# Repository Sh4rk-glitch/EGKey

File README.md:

# EGKey (ErgoKey)

A custom ergonomic keyboard PCB design using Choc-style hotswap sockets, a face-down Promicro footprint, and an optional OLED. This repository contains KiCad board sources, generated gerbers, mechanical DXF outlines, and footprint helper scripts driven by a YAML configuration.

---

# Files

## CAD
Inside `EGKey main file` there are many different files below is what is most important and how to get there: 
Starting off with the CAD files, the CAD is under `CAD files`. The main CAD file is `case. step`, if you want the other CAD files then click on `cases` and the rest are in there.
To see the outlines for the CAD go to `config.yaml` and then `output` and then `outlines`.

## PCBs
The PCBs are under `pcbs` then going to `ALL PCBS`. The main PCB file is `EGKeyMasterPCB`, if you wish to see the no routing and my previous attempts at routing then click on `EGKey-noRouting` and `EGKeyPCB-routingV2`.
The gerber file is under `pcbs` then click on the `EGKeyGerb` file, it's a zip file so it'll download as a zip.
Under `config.yaml` the footprint for the mounting hole is there under `footprints` and then its the only file under there.

## Firmware
To get to the firmware file, click on `firmware` which will be under `EGKey main file` and then inside `firmware` will be all the firmware writting for EGKey.

## Bill of Materials
  Part                                 Count                     Cost
- PCB Fab (With Shipping)	               1	                  $30.00 USD
- Arduino Pro Micro	                     1	                  $10.00 USD
- OLED Display	                         1	                   $4.00 USD
- Kailh Choc v2 Switches	               6 (58 Keys Total)	  $30.00 USD
- 1N4148 Diodes (SMD)	                   6 (58 Diodes Total)	 $2.00 USD
- Kailh Choc Hotswap Sockets	           6 (58 Sockets Total)	$10.00 USD
- Reset Switch (SMD, 4 Pin, Flat)	       1	                   $0.50 USD
- Mill Max Sockets & Pins	               1	                   $7.50 USD
- Medium Profile Controller Socket	     1	                   $0.50 USD
- Choc v1 Keycaps	                       1	                  $50-75 USD

Total: $140-160 USD

---
# Pictures:
## PCBs:

## CAD:

All images are located on my journal, at:
[https://blueprint.hackclub.com/projects/5019](url)

If you have any questions, email me at shouryamishra011@gmail.com

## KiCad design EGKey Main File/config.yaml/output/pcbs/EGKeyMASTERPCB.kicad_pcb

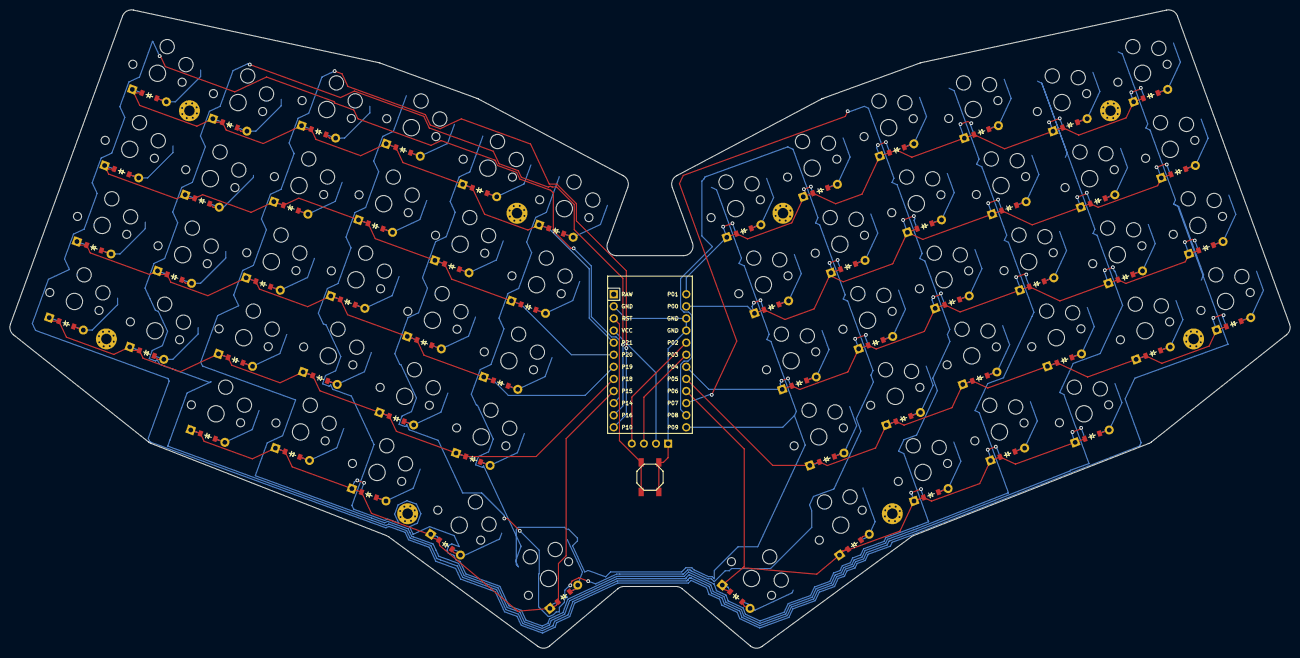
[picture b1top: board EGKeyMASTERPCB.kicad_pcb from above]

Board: 2 copper layers, 268.9 x 134.0 mm, 127 parts (0 on the bottom side), 79 nets.

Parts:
B1: SW_TACT_ALPS_SKQGABE010
D1, D2, D3, D4, D5, D6, D7, D8, D9, D10, D11, D12, D13, D14, D15, D16, D17, D18, D19, D20, D21, D22, D23, D24, D25, D26, D27, D28, D29, D30, D31, D32, D33, D34, D35, D36, D37, D38, D39, D40, D41, D42, D43, D44, D45, D46, D47, D48, D49, D50, D51, D52, D53, D54, D55, D56, D57, D58: ComboDiode
MCU1: ProMicro
OLED1: OLED; OLED_headers
S1, S2, S3, S4, S5, S6, S7, S8, S9, S10, S11, S12, S13, S14, S15, S16, S17, S18, S19, S20, S21, S22, S23, S24, S25, S26, S27, S28, S29, S30, S31, S32, S33, S34, S35, S36, S37, S38, S39, S40, S41, S42, S43, S44, S45, S46, S47, S48, S49, S50, S51, S52, S53, S54, S55, S56, S57, S58: PG1350
_1, _2, _3, _4, _5, _6, _7, _8: MountingHole_2.2mm_M2_Pad_Via

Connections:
GND: B1.1, MCU1.2, MCU1.15, MCU1.16, OLED1.1
P0: D32.1, D36.1, D41.1, D46.1, D51.1, D55.1, MCU1.14
P1: D33.1, D37.1, D42.1, D47.1, D52.1, D56.1, MCU1.13
P2: MCU1.17, OLED1.4
P3: MCU1.18, OLED1.3
P4: D31.1, D35.1, D40.1, D45.1, D50.1, D54.1, MCU1.19
P5: D30.1, D34.1, D39.1, D44.1, D49.1, D53.1, MCU1.20
P6: D38.1, D43.1, D48.1, D57.1, D58.1, MCU1.21
P7: MCU1.22, S15.1, S16.1, S17.1, S18.1, S19.1, S44.1, S45.1, S46.1, S47.1, S48.1
P8: MCU1.23, S20.1, S21.1, S22.1, S23.1, S28.1, S49.1, S50.1, S51.1, S52.1, S57.1
P9: MCU1.24, S24.1, S25.1, S26.1, S27.1, S29.1, S53.1, S54.1, S55.1, S56.1, S58.1
P10: MCU1.12, S10.1, S11.1, S12.1, S13.1, S14.1, S39.1, S40.1, S41.1, S42.1, S43.1
P14: MCU1.10, S1.1, S2.1, S3.1, S4.1, S30.1, S31.1, S32.1, S33.1
P15: D9.1, D14.1, D19.1, D28.1, D29.1, MCU1.9
P16: MCU1.11, S5.1, S6.1, S7.1, S8.1, S9.1, S34.1, S35.1, S36.1, S37.1, S38.1
P18: D1.1, D5.1, D10.1, D15.1, D20.1, D24.1, MCU1.8
P19: D2.1, D6.1, D11.1, D16.1, D21.1, D25.1, MCU1.7
P20: D3.1, D7.1, D12.1, D17.1, D22.1, D26.1, MCU1.6
P21: D4.1, D8.1, D13.1, D18.1, D23.1, D27.1, MCU1.5
RST: B1.2, MCU1.3
VCC: MCU1.4, OLED1.2
index_bottom: D20.2, S20.2
index_home: D21.2, S21.2
index_mod: D19.2, S19.2
index_num: D23.2, S23.2
index_top: D22.2, S22.2
inner_bottom: D24.2, S24.2
inner_home: D25.2, S25.2
inner_num: D27.2, S27.2
inner_top: D26.2, S26.2
layer_cluster: D28.2, S28.2
middle_bottom: D15.2, S15.2
middle_home: D16.2, S16.2
middle_mod: D14.2, S14.2
middle_num: D18.2, S18.2
middle_top: D17.2, S17.2
mirror_index_bottom: D49.2, S49.2
mirror_index_home: D50.2, S50.2
mirror_index_mod: D48.2, S48.2
mirror_index_num: D52.2, S52.2
mirror_index_top: D51.2, S51.2
mirror_inner_bottom: D53.2, S53.2
mirror_inner_home: D54.2, S54.2
mirror_inner_num: D56.2, S56.2
mirror_inner_top: D55.2, S55.2
mirror_layer_cluster: D57.2, S57.2
mirror_middle_bottom: D44.2, S44.2
mirror_middle_home: D45.2, S45.2
mirror_middle_mod: D43.2, S43.2
mirror_middle_num: D47.2, S47.2
mirror_middle_top: D46.2, S46.2
mirror_outer_bottom: D30.2, S30.2
mirror_outer_home: D31.2, S31.2
mirror_outer_num: D33.2, S33.2
mirror_outer_top: D32.2, S32.2
mirror_pinky_bottom: D34.2, S34.2
mirror_pinky_home: D35.2, S35.2
mirror_pinky_num: D37.2, S37.2
mirror_pinky_top: D36.2, S36.2
mirror_ring_bottom: D39.2, S39.2
mirror_ring_home: D40.2, S40.2
mirror_ring_mod: D38.2, S38.2
mirror_ring_num: D42.2, S42.2
mirror_ring_top: D41.2, S41.2
mirror_space_cluster: D58.2, S58.2
outer_bottom: D1.2, S1.2
outer_home: D2.2, S2.2
outer_num: D4.2, S4.2
outer_top: D3.2, S3.2
pinky_bottom: D5.2, S5.2
pinky_home: D6.2, S6.2
pinky_num: D8.2, S8.2
pinky_top: D7.2, S7.2
ring_bottom: D10.2, S10.2
ring_home: D11.2, S11.2
ring_mod: D9.2, S9.2
ring_num: D13.2, S13.2
ring_top: D12.2, S12.2
space_cluster: D29.2, S29.2

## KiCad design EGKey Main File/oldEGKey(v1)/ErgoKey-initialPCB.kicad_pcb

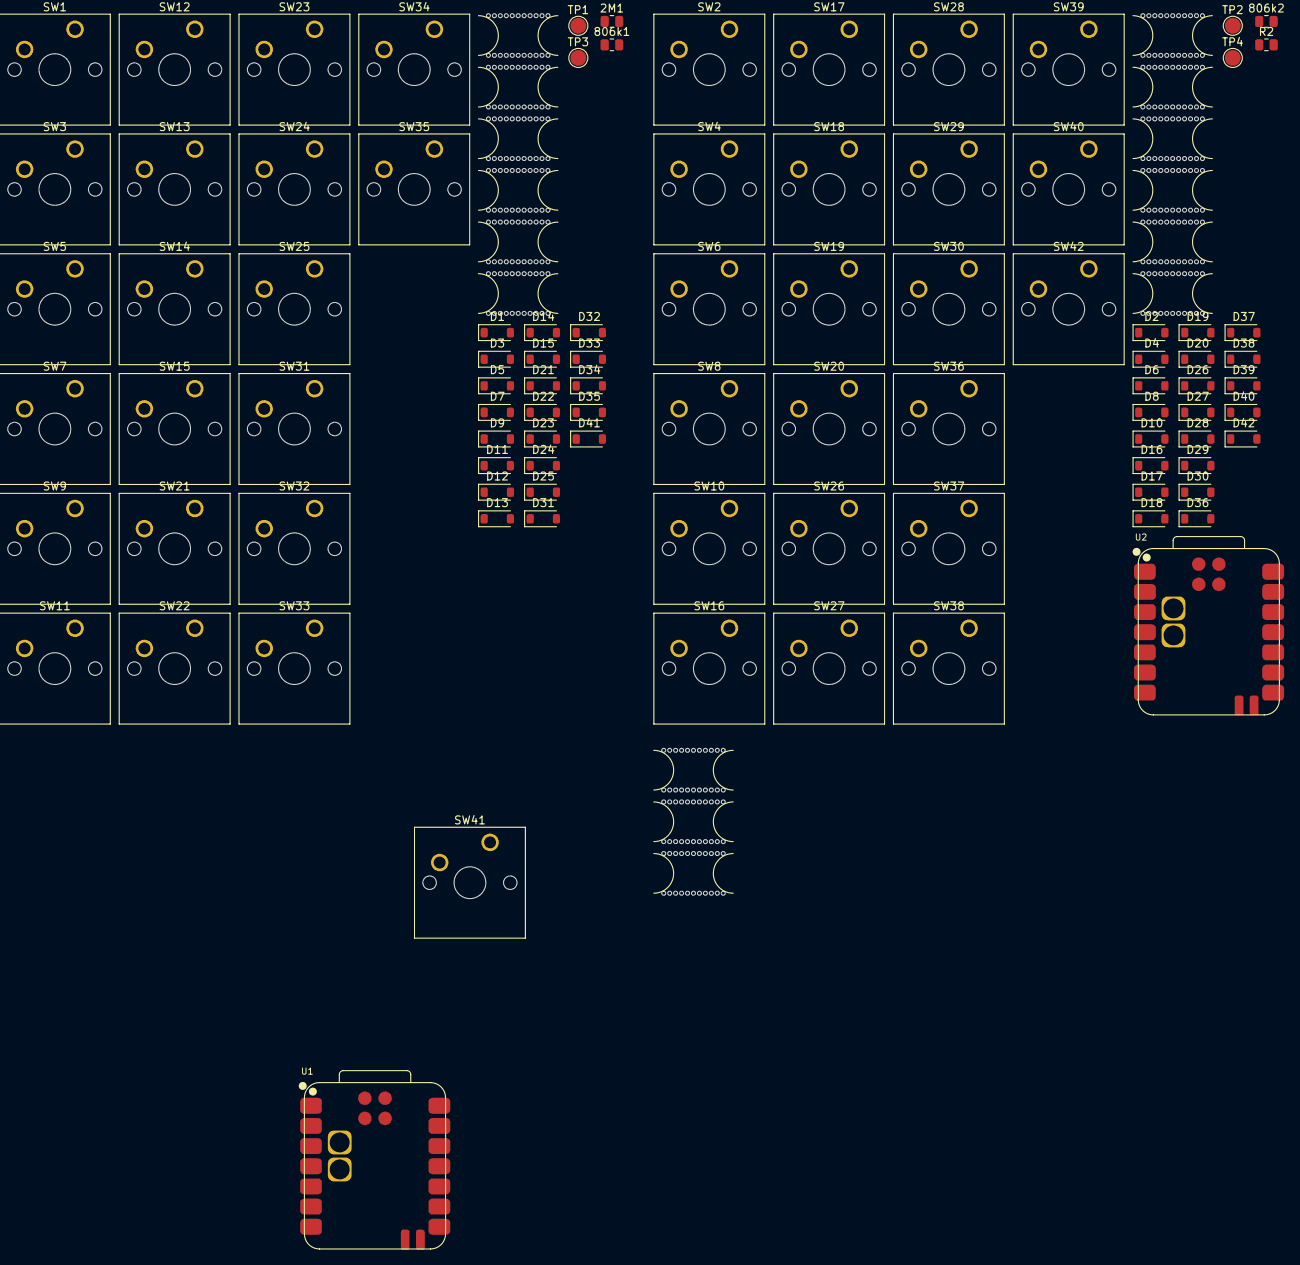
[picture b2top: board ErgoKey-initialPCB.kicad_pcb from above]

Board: 2 copper layers, 109 parts (0 on the bottom side), 23 nets, no tracks yet.

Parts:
2M1, 806k2: R3; R_0805_2012Metric
806k1: R; R_0805_2012Metric
BO1, BO2, BO3: break off; mouse-bite-5mm-slot
D1, D2, D3, D4, D5, D6, D7, D8, D9, D10, D11, D12, D13, D14, D15, D16, D17, D18, D19, D20, D21, D22, D23, D24, D25, D26, D27, D28, D29, D30, D31, D32, D33, D34, D35, D36, D37, D38, D39, D40, D41, D42: D; D_SOD-123
H1, H2, H3, H4, H5, H6, H7, H8, H9, H10, H11, H12: mouse-bite-5mm-slot
R2: R; R_0805_2012Metric
SW1, SW2, SW3, SW4, SW5, SW6, SW7, SW8, SW9, SW10, SW11, SW12, SW13, SW14, SW15, SW16, SW17, SW18, SW19, SW20, SW21, SW22, SW23, SW24, SW25, SW26, SW27, SW28, SW29, SW30, SW31, SW32, SW33, SW34, SW35, SW36, SW37, SW38, SW39, SW40, SW41, SW42: SW_Push; SW_Cherry_MX_1.00u_PCB
TP1, TP2: bat; TestPoint_Pad_D2.0mm
TP3, TP4: GND; TestPoint_Pad_D2.0mm
U1, U2: XIAO-nRF52840-SMD; modified-XIAO-nRF52840-SMD

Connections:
/Left/BT_PIN: 806k1.2, U1.1 (P0.02_A0_D0)
/Left/COL0: SW11.1, SW21.1, SW31.1, U1.2 (P0.03_A1_D1)
/Left/COL1: SW12.1, SW22.1, SW32.1, U1.3 (P0.28_A2_D2)
/Left/COL2: SW13.1, SW23.1, SW33.1, U1.4 (P0.29_A3_D3)
/Left/COL3: SW14.1, SW24.1, SW34.1, U1.5 (P0.04_A4_D4_SDA)
/Left/COL4: SW15.1, SW25.1, SW35.1, SW41.1, U1.6 (P0.05_A5_D5_SCL)
/Left/ROW0: D3.1 (K), D5.1 (K), D7.1 (K), D9.1 (K), U1.11 (P1.15_D10_MOSI)
/Left/ROW1: D12.1 (K), D13.1 (K), D14.1 (K), D15.1 (K), U1.10 (P1.14_D9_MISO)
/Left/ROW2: D22.1 (K), D23.1 (K), D24.1 (K), D25.1 (K), U1.9 (P1.13_D8_SCK)
/Left/ROW3: D32.1 (K), D33.1 (K), D34.1 (K), D35.1 (K), U1.8 (P1.12_D7_RX)
/Left/VBAT: TP1.1, U1.15 (BAT)
/Right/BT_PIN: R2.2, U2.1 (P0.02_A0_D0)
/Right/COL0: SW16.1, SW26.1, SW36.1, U2.2 (P0.03_A1_D1)
/Right/COL1: SW17.1, SW27.1, SW37.1, U2.3 (P0.28_A2_D2)
/Right/COL2: SW18.1, SW28.1, SW38.1, U2.4 (P0.29_A3_D3)
/Right/COL3: SW19.1, SW29.1, SW39.1, U2.5 (P0.04_A4_D4_SDA)
/Right/COL4: SW20.1, SW30.1, SW40.1, SW42.1, U2.6 (P0.05_A5_D5_SCL)
/Right/ROW0: D4.1 (K), D6.1 (K), D8.1 (K), D10.1 (K), U2.11 (P1.15_D10_MOSI)
/Right/ROW1: D17.1 (K), D18.1 (K), D19.1 (K), D20.1 (K), U2.10 (P1.14_D9_MISO)
/Right/ROW2: D27.1 (K), D28.1 (K), D29.1 (K), D30.1 (K), U2.9 (P1.13_D8_SCK)
/Right/ROW3: D37.1 (K), D38.1 (K), D39.1 (K), D40.1 (K), U2.8 (P1.12_D7_RX)
/Right/VBAT: TP2.1, U2.15 (BAT)
GND: 806k2.2, TP3.1, TP4.1, U1.13 (GND), U1.16 (GND), U2.13 (GND), U2.16 (GND)

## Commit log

2025-12-06 Creating repo
2025-12-06 Adding EGKey Main Files
2025-12-06 Update README with project description
    Added project description and details about the PCB design.
2025-12-06 Revise README for improved project documentation
    Updated README to enhance clarity and detail about the EGKey project, including repository layout, features, and workflow instructions.
2025-12-06 Remove 'Releases' section from README
    Removed the 'Releases' section from the README.
2025-12-06 Updating Case CAD
2025-12-06 Add Bill of Materials to README
    Added a Bill of Materials section with detailed parts list and costs.
2025-12-07 Revise README structure and content
    Updated README to improve structure and clarity, including sections for CAD, PCBs, Firmware, and Fabrication Tips.
2025-12-07 Update README to clarify CAD files section
    Clarified the section about CAD files in the README.
2025-12-07 Revise README structure and section titles
    Updated file structure and section headers in README.
2025-12-07 Refactor README section headers
    Updated section headers in README for clarity and consistency.
2025-12-07 Upload Software and redo formatting for files
2025-12-07 Add images for PCBs and CAD in README
    Added pictures of PCBs and CAD to the README.
2025-12-09 Adding PCB, CAD, and firmware to front page
2025-12-09 Adding BOM file
2025-12-09 Convert BOM to CSV format
    Converted BOM entries to CSV format with comma separation.
2025-12-09 Fix formatting and add spaces in BOM.csv
2025-12-09 Update BOM.csv to include headers and format URLs
2025-12-09 Remove duplicate entries in BOM.csv
2025-12-09 Add missing entries to BOM.csv
    Added missing BOM entries for components.
2025-12-09 Revise product entries and URLs in BOM.csv
    Updated product links and descriptions in BOM.csv.
2025-12-09 Update BOM.csv with new product links and formatting
2025-12-09 Revise BOM.csv with updated product information
    Updated BOM.csv with new product links and details.
